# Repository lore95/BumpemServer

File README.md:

# bumpem

Host software for the IBMS Bump'em multi-directional perturbation system.

## Quick start
```sh
git clone <repo> && cd bumpem
python -m venv .venv && source .venv/bin/activate   # or conda
pip install -e ".[dev]"
pytest                                   # no hardware needed
bumpem monitor --sim                     # simulated board
```

## With hardware
No person attached for first tests. Stop the treadmill before `release` or `estop`.
```sh
pip install platformio
scripts/flash.sh                         # firmware v1  (scripts/flash.sh legacy = v0 reference)
bumpem ports                             # find the Teensy
bumpem info  --port /dev/tty.usbmodemXXXX
bumpem arm   --port /dev/tty.usbmodemXXXX --watch 3     # ramp to 5 N baseline
bumpem pulse A=95 --rise 50 --dur 600 --fall 0 --port /dev/tty.usbmodemXXXX --watch 2
bumpem release --port /dev/tty.usbmodemXXXX              # ramp to 0, drivers off
bumpem estop   --port /dev/tty.usbmodemXXXX              # drivers off now
```
Pulse amplitudes are relative to baseline. Protocol and parameters: `docs/PROTOCOL.md`.

ESCON setup is still done once in ESCON Studio. See `escon/README.md` and `docs/thesis/manual.pdf` §4.3.1.

Docs: `docs/knowledge/` (system facts), `docs/PROTOCOL.md`, `docs/STATUS.md`.

## Server
```sh
pip install -e ".[server,dev]"
bumpem serve --board sim                      # or --board /dev/tty.usbmodemXXXX
```
Open http://127.0.0.1:8000/docs to try every endpoint from the browser. API contract: `docs/API.md`.
While the server runs it owns the serial port: stop the board through the API (`POST /api/v1/estop`), not the CLI.

License: proprietary to IBMS (Institute for Advanced Biomechanics and Motion Studies, Hochschule Offenburg), non-commercial academic use only. See `LICENSE`.

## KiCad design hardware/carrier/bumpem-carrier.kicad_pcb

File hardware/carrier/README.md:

# Carrier board (v1)

Replaces the breadboard: Teensy 4.1 and the MCP4728 DAC plug into sockets, each cable module gets one 5-way **pluggable** connector: its wires are screwed into a plug once, the plug pops into the board and locks with two screws.
Same connections as `docs/diagrams/cabling-4-modules.png`, plus a protection network on each force input.

*Top view without the ground fill. Red = top copper, blue = bottom copper, yellow = silkscreen. Module wires enter at the bottom edge.*

## What is on it
| Part | Connects |
|---|---|
| U1 Teensy 4.1 (socket, USB at the left edge) | enable T27–30, force T14–17, I²C T18 SDA / T19 SCL, 3V3, GND. **VIN/5V not connected** |
| U2 Adafruit MCP4728 (socket) | VA–VD → setpoint of modules A–D, VCC 3.3 V from the Teensy |
| J1–J4 pluggable headers, one per module (A left, B front, C right, D back), pins left to right | 1 EN yellow · 2 SP+ blue · 3 SP− green · 4 GND white · 5 F brown |
| R1–R4 1 kΩ (series), R5–R8 1 MΩ (pull-down), D1–D4 BAT85 (clamp to 3.3 V) | per force input: connector F → 1 kΩ → Teensy pin; 1 MΩ to GND; BAT85 to 3.3 V |

Board 154 × 96 mm, 2 layers, through-hole parts only, 0.5 mm tracks (0.8 mm for 3.3 V), only 45° bends, ground fill on both layers (0.5 mm from other copper), 4 × M3 holes.
Spacing (measured, edge to edge): ≥ 0.74 mm between any two nets; 0.74 mm is the gap between neighbouring socket pins (2.54 mm headers).
The force tracks run under the Teensy and out past its right end, never between socket pins: ≥ 1.39 mm to any other net's pad, so a solder blob on a socket cannot reach a force signal.

**Force inputs.** The IAA100 amplifiers are trimmed to 0–3.3 V = 0–200 N (`docs/knowledge/calibration.md`). With 1 kΩ / 1 MΩ the Teensy sees 99.9 % of that (no recalibration needed). An unplugged input reads 0 N, as the ground jumpers do today. The diode only acts on a fault (amplifier mis-set or miswired): the 1 kΩ limits the current, the BAT85 dumps it into 3.3 V. If an amplifier can only be set to 0–10 V, change the pair to a divider (e.g. 22 kΩ series / 10 kΩ pull-down → 3.1 V) and recalibrate.

## Order (PCB maker)
1. Upload `fab/bumpem-carrier-gerbers.zip` to JLCPCB, Aisler, PCBWay or similar. Defaults are fine: 2 layers, 1.6 mm, any colour, HASL. The design uses no tight rules (smallest drill 0.8 mm).
2. Buy the parts below (or ask the makerspace for them).

| Qty | Part | Note |
|---|---|---|
| 1 | PCB from step 1 | |
| 2 | female header 1 × 24, 2.54 mm, 8.5 mm tall | Teensy socket (or cut from 1 × 40 strips) |
| 2 | female header 1 × 6, 2.54 mm | DAC socket |
| 4 | Phoenix Contact header **MSTB 2,5/5-GF-5,08 (1776537)**, threaded flange | on the board |
| 4 | Phoenix Contact plug **MSTB 2,5/5-STF-5,08 (1778014)**, screw flange | on each module cable: wires screwed in once (1 EN, 2 SP+, 3 SP−, 4 GND, 5 F) |
| optional | Phoenix Contact coding profile **CP-MSTB (1734634)** | keys each socket to its own plug (A's cable can't go into C's socket); check the coding scheme in Phoenix's MSTB coding guide |
| 4 | resistor 1 kΩ, 0.25 W, 1 %, axial | R1–R4 |
| 4 | resistor 1 MΩ, 0.25 W, 1 %, axial | R5–R8 |
| 4 | BAT85 Schottky diode, DO-35 | D1–D4, band (cathode) towards the 3.3 V track |
| 4 | M3 spacer + screw | |

Full list: `fab/bumpem-carrier-bom.csv`. Schematic: `fab/bumpem-carrier-schematic.pdf`. Layout: `fab/bumpem-carrier-top.pdf`, `fab/bumpem-carrier-bottom.pdf` (seen from below), both layers together `fab/bumpem-carrier-layout.pdf`. Whole KiCad project: `fab/bumpem-carrier-kicad.zip`.
**As built (2026-10-26, D23):** D1–D4 places hold **1 MΩ to 3.3 V** (not BAT85) and **R5–R8 are empty**, on purpose: a loose force cable then reads ≈ 200 N → motor 0 A + FAULT. Do not fit R5–R8.
**Soldering guide:** `fab/bumpem-carrier-soldering.pdf` (what each part looks like + German drawer names, steps 1–9 one part per page (top: where it goes, bottom: which pads), top and solder side drawn from the board, part order, diode band, extra top-side joints if the holes are not plated, checks). Rebuild: `$KPY dump_board.py bumpem-carrier.kicad_pcb fab/board.json`, then `python soldering_guide.py`.

**Makerspace HS Offenburg (reply 2026-10-05):** can make the board, but **without solder mask and silkscreen** (bare copper): fine for a prototype. Open with them: plated through-holes / vias? (the top-layer tracks end on socket pads, which cannot be soldered from the top under a socket); how to label pins without silkscreen (copper text or a printed label sheet).

## Assembly and first power-up
1. Solder the low parts first: resistors, diodes (check the band!), then the female headers, then the 4 MSTB headers (plug side at the board edge).
   **Sockets on the board are female; the male pins belong on the Teensy and the DAC** (the lab's Teensy and DAC already have them: they sit in the breadboard). Never solder male pins into the board: male meets male and nothing plugs in. Teensy and DAC are never soldered to the board, so either can be swapped. To keep the sockets straight while soldering, plug spare male pin strips into them (other ends in a breadboard) instead of the Teensy; solder one pin per end, check flat, then the rest.
2. **No Teensy, no DAC, no modules.** Multimeter beep test: 3V3 ↔ GND must **not** beep; each connector pin 3 and 4 ↔ Teensy GND must beep; connector A pin 1 ↔ Teensy socket pin 27 must beep (same for B–D: 28, 29, 30).
3. Plug in the DAC and the Teensy (USB at the board edge). USB only, no modules: `bumpem info --port <PORT>` must answer.
4. One module at a time, 48 V off: screw that module's 5 wires into a plug (order as printed on the board: EN yellow, SP+ blue, SP− green, GND white, F brown), plug it in, tighten the two flange screws. Then repeat `scripts/open_loop_test.sh` for that module.

## Before ordering: check in KiCad (5 minutes)
- Open `bumpem-carrier.kicad_pro` → PCB editor → View → 3D viewer: the MSTB headers' plug openings must face the bottom board edge.
- Hold a Teensy and the DAC over a 1:1 print of `fab/bumpem-carrier-layout.pdf`: pins over the holes, Teensy USB at the left edge.

## Change the design
Do not edit the KiCad files by hand; they are generated.
- Connections and part values: `netlist.py`. Placement and routing: `gen_carrier.py`. Schematic drawing: `gen_schematic.py`.
- Rebuild and check everything: `./build.sh` (needs KiCad 8). It must print 0 ERC violations and 0 DRC / schematic-parity violations.

Sources: Teensy 4.1 pin order from XenGi/teensy_library (MIT); MCP4728 breakout pad positions from adafruit/Adafruit-MCP4728-PCB; pins from `firmware/src/main.ino` and `docs/knowledge/wiring.md`.

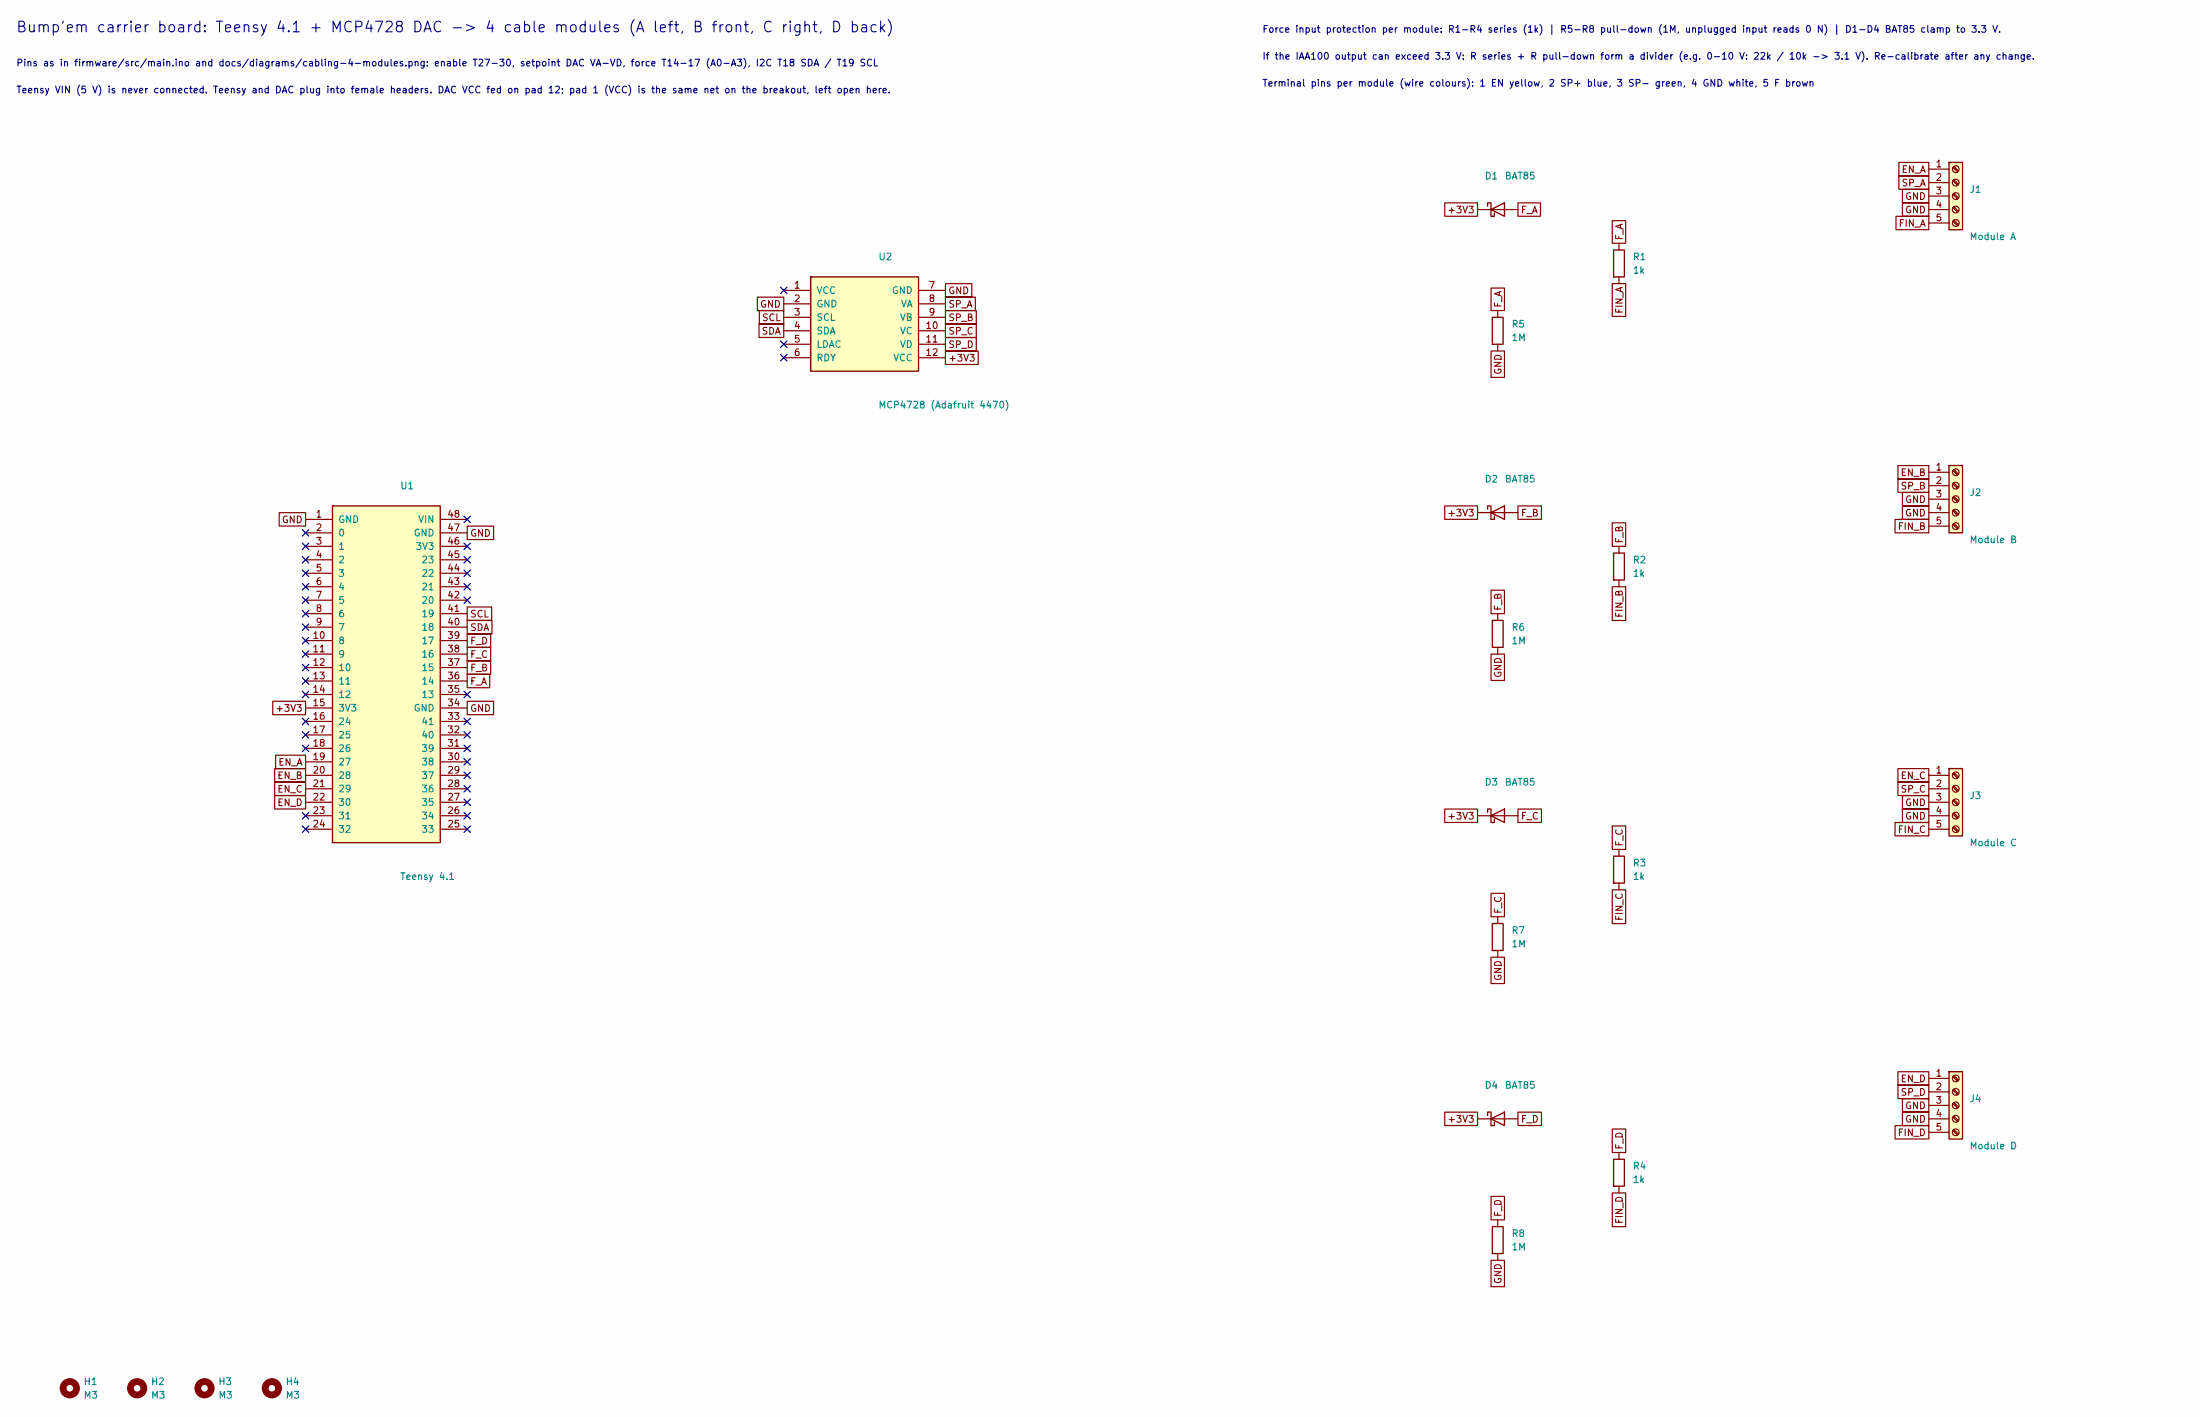
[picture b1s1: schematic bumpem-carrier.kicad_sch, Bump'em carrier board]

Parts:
D1, D2, D3, D4: BAT85; D_DO-35_SOD27_P7.62mm_Horizontal
H1, H2, H3, H4: M3; MountingHole_3.2mm_M3
J1: Module A; PhoenixContact_MSTB_2,5_5-GF-5,08_1x05_P5.08mm_Horizontal_T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
J2: Module B; PhoenixContact_MSTB_2,5_5-GF-5,08_1x05_P5.08mm_Horizontal_T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
J3: Module C; PhoenixContact_MSTB_2,5_5-GF-5,08_1x05_P5.08mm_Horizontal_T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
J4: Module D; PhoenixContact_MSTB_2,5_5-GF-5,08_1x05_P5.08mm_Horizontal_T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
R1, R2, R3, R4: 1k; R_Axial_DIN0207_L6.3mm_D2.5mm_P10.16mm_Horizontal
R5, R6, R7, R8: 1M; R_Axial_DIN0207_L6.3mm_D2.5mm_P7.62mm_Horizontal
U1: Teensy 4.1; Teensy41_Socket
U2: MCP4728 (Adafruit 4470); Adafruit_MCP4728_Socket

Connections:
+3V3: D1.1 (K), D2.1 (K), D3.1 (K), D4.1 (K), U1.15 (3V3), U2.12 (VCC)
EN_A: J1.1, U1.19 (27)
EN_B: J2.1, U1.20 (28)
EN_C: J3.1, U1.21 (29)
EN_D: J4.1, U1.22 (30)
FIN_A: J1.5, R1.2
FIN_B: J2.5, R2.2
FIN_C: J3.5, R3.2
FIN_D: J4.5, R4.2
F_A: D1.2 (A), R1.1, R5.1, U1.36 (14)
F_B: D2.2 (A), R2.1, R6.1, U1.37 (15)
F_C: D3.2 (A), R3.1, R7.1, U1.38 (16)
F_D: D4.2 (A), R4.1, R8.1, U1.39 (17)
GND: J1.3, J1.4, J2.3, J2.4, J3.3, J3.4, J4.3, J4.4, R5.2, R6.2, R7.2, R8.2, U1.1 (GND), U1.34 (GND), U1.47 (GND), U2.2 (GND), U2.7 (GND)
SCL: U1.41 (19), U2.3 (SCL)
SDA: U1.40 (18), U2.4 (SDA)
SP_A: J1.2, U2.8 (VA)
SP_B: J2.2, U2.9 (VB)
SP_C: J3.2, U2.10 (VC)
SP_D: J4.2, U2.11 (VD)

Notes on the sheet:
Bump'em carrier board: Teensy 4.1 + MCP4728 DAC -> 4 cable modules (A left, B front, C right, D back)
Pins as in firmware/src/main.ino and docs/diagrams/cabling-4-modules.png: enable T27-30, setpoint DAC VA-VD, force T14-17 (A0-A3), I2C T18 SDA / T19 SCL
Teensy VIN (5 V) is never connected. Teensy and DAC plug into female headers. DAC VCC fed on pad 12; pad 1 (VCC) is the same net on the breakout, left open here.
Force input protection per module: R1-R4 series (1k) | R5-R8 pull-down (1M, unplugged input reads 0 N) | D1-D4 BAT85 clamp to 3.3 V.
If the IAA100 output can exceed 3.3 V: R series + R pull-down form a divider (e.g. 0-10 V: 22k / 10k -> 3.1 V). Re-calibrate after any change.
Terminal pins per module (wire colours): 1 EN yellow, 2 SP+ blue, 3 SP- green, 4 GND white, 5 F brown

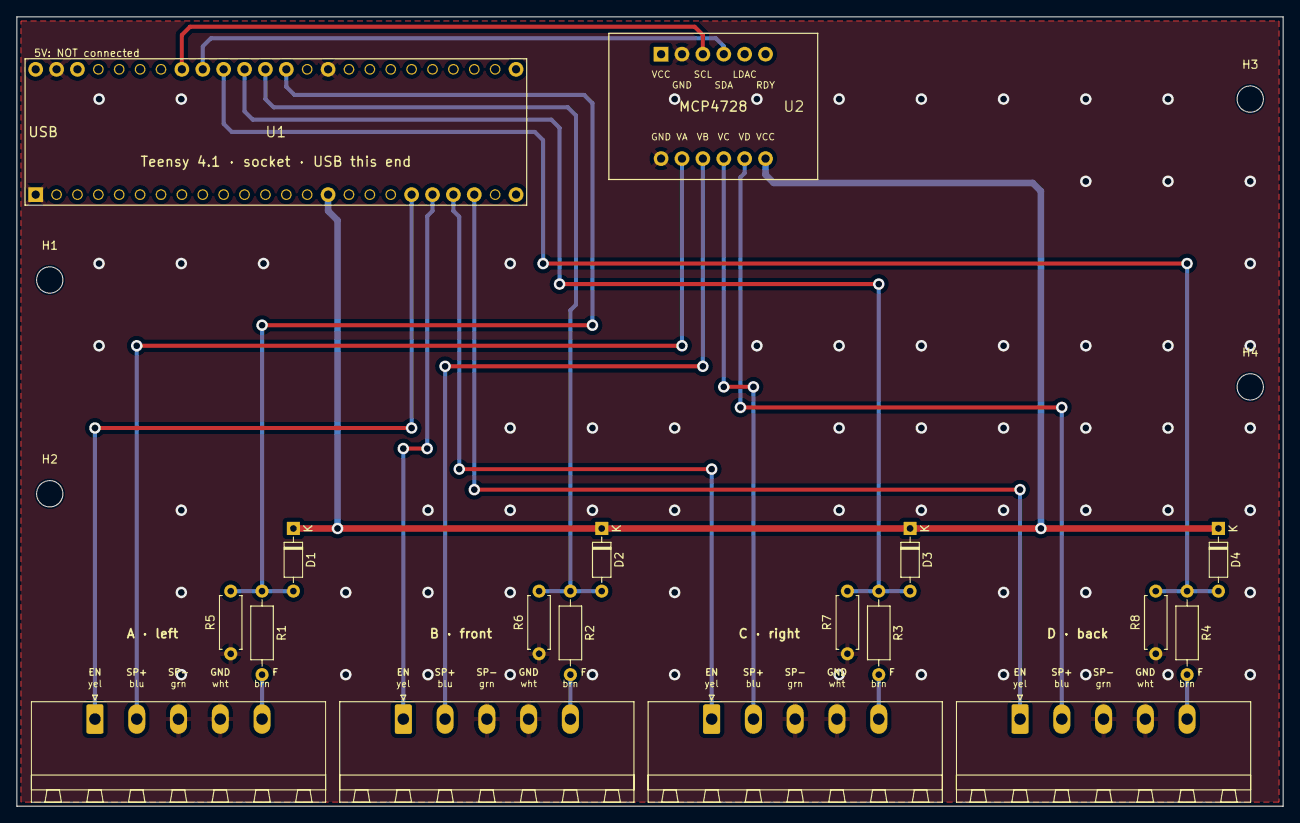
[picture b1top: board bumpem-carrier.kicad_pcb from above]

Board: 2 copper layers, 154.0 x 96.0 mm, 22 parts (0 on the bottom side), 20 nets.

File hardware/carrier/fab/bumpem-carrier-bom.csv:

"Reference","Value","Footprint","QUANTITY"
"D1-D4","BAT85","Diode_THT:D_DO-35_SOD27_P7.62mm_Horizontal","4"
"J1","Module A","Connector_Phoenix_MSTB:PhoenixContact_MSTB_2,5_5-GF-5,08_1x05_P5.08mm_Horizontal_ThreadedFlange","1"
"J2","Module B","Connector_Phoenix_MSTB:PhoenixContact_MSTB_2,5_5-GF-5,08_1x05_P5.08mm_Horizontal_ThreadedFlange","1"
"J3","Module C","Connector_Phoenix_MSTB:PhoenixContact_MSTB_2,5_5-GF-5,08_1x05_P5.08mm_Horizontal_ThreadedFlange","1"
"J4","Module D","Connector_Phoenix_MSTB:PhoenixContact_MSTB_2,5_5-GF-5,08_1x05_P5.08mm_Horizontal_ThreadedFlange","1"
"R1-R4","1k","Resistor_THT:R_Axial_DIN0207_L6.3mm_D2.5mm_P10.16mm_Horizontal","4"
"R5-R8","1M","Resistor_THT:R_Axial_DIN0207_L6.3mm_D2.5mm_P7.62mm_Horizontal","4"
"U1","Teensy 4.1","bumpem-carrier:Teensy41_Socket","1"
"U2","MCP4728 (Adafruit 4470)","bumpem-carrier:Adafruit_MCP4728_Socket","1"

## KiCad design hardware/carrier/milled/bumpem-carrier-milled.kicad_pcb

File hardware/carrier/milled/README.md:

# Carrier board, makerspace version (single-sided)

For the HS Offenburg makerspace's PCB mill: one copper layer, no plating, no solder mask, no copper fill.
Same outline, mounting holes and Teensy / DAC / plug positions as v1 (`../`), so the printed carrier plate fits and every cable plug goes in the same place.

**To make it:** send `fab/bumpem-carrier-milled.zip`. Its `gerbers/` folder is what the mill needs (bottom copper, outline, one drill file with all 114 holes, `MAKERSPACE.txt` in German and English: mill the bottom only, remove the unused copper, drill every hole). The PDFs are the 1:1 bottom view, the parts placement and the soldering guide; `bumpem-carrier-milled-sides.png` shows both sides assembled (`render_milled.py`).

## Why it is easier to solder
- **Everything is soldered on the bottom**: 70 joints, nothing on the top, no vias.
- **No ground fill**: around each pad there is bare board, so solder that misses the pad does not stick. Ask the makerspace to remove the unused copper (rub-out); otherwise isolation ≥ 0.6 mm.
- **Unused socket pins are bare holes** (no copper): nothing to solder, nothing to short. VIN cannot touch anything.
- **7 wire links** (W1–W7, insulated wire on the top, soldered underneath) instead of vias: W1 SDA, W2 SCL (crosses W1), W3 3.3 V, W4 enable B, W5–W7 setpoint A–C.
- The **1 kΩ resistors bridge tracks** too (their bodies cross the tracks between their pads). R2 has 15.24 mm leg spacing.
- Copper letters A–D next to each plug (bottom side).

## Circuit (differences from v1, D24)
Same pins as v1 (`../netlist.py`): Teensy 27–30 enable, 14–17 force, 18/19 I²C, DAC VA–VD setpoints.
Force input: plug pin 5 → 1 kΩ → Teensy pin; **1 MΩ from plug pin 5 to the same module's enable line** (plug pin 1). Armed (enable high) a loose force cable reads ≈ 200 N → that motor 0 A and over-force FAULT, as the v1 board as built (D23); disarmed it reads 0 N. No diodes, no pull-down. With the amplifier connected the 1 MΩ changes nothing measurable.
DAC ground through its row-1 GND pin only (both GND pins are joined on the breakout).

## Layout (hand-planned, `gen_milled.py`)
Ground runs round the outside: left edge, a bus under the plugs (pins 3 and 4 from below), right edge, top edge to the DAC.
Force lines go up over the Teensy's far row (F_D outermost) and come down between the Teensy and the DAC in A–D order; I²C and 3.3 V run under the Teensy and cross them on W1–W3.
Below: lanes top → bottom SP_D, EN_A, F_D, F_C, F_B, EN_D, EN_C, SP_A, FIN_A, SP_B; jumps: R1 over EN_D EN_C SP_A, R2 over EN_D EN_C SP_A SP_B, R3 over EN_D, R4 over SP_D, W5/W6 over F_D F_C EN_D EN_C, W7 over F_D F_C EN_D, W4 over SP_A FIN_A; the pull-ups R5–R8 bridge each plug's setpoint track.
(`gen_milled.py` also holds a grid router with wire-link moves; it is not used for the final layout: greedy routing needed 7–17 links and boxed nets in.)

## Build and check
`./build_milled.sh` (KiCad 8; `python3` with matplotlib for the guide): generates the board, runs DRC (must print 0 violations; the 7 "unconnected" items are W1–W7, which KiCad cannot see as wires), runs `check_milled.py` (every net one piece, counting the wire links: must print "all connected"), writes `fab/`.

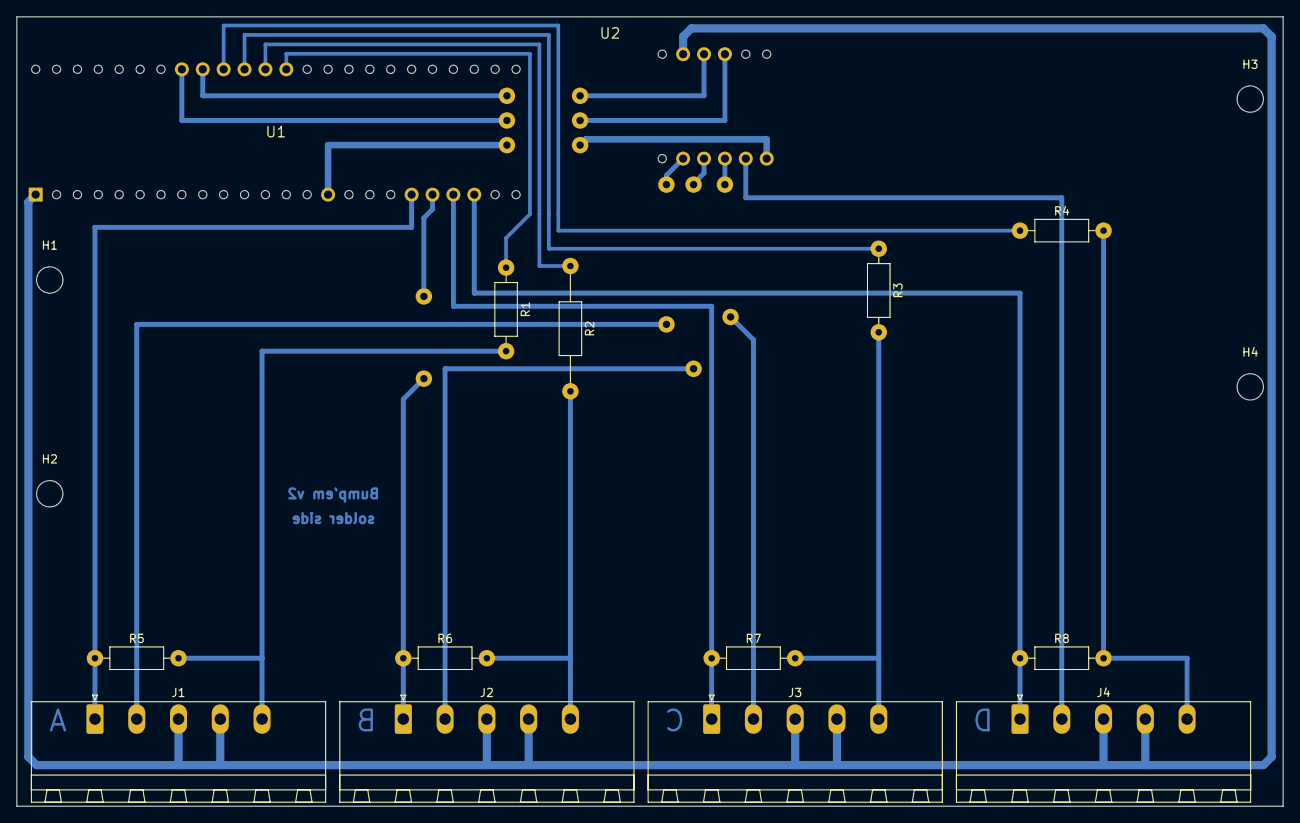
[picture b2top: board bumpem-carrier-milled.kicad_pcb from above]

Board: 2 copper layers, 154.0 x 96.0 mm, 25 parts (0 on the bottom side), 20 nets.

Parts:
H1, H2, H3, H4: M3; MountingHole_3.2mm_M3
J1: Module A; PhoenixContact_MSTB_2,5_5-GF-5,08_1x05_P5.08mm_Horizontal_T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
J2: Module B; PhoenixContact_MSTB_2,5_5-GF-5,08_1x05_P5.08mm_Horizontal_T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
J3: Module C; PhoenixContact_MSTB_2,5_5-GF-5,08_1x05_P5.08mm_Horizontal_T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
J4: Module D; PhoenixContact_MSTB_2,5_5-GF-5,08_1x05_P5.08mm_Horizontal_T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
R1, R3, R4: 1k; R_Axial_DIN0207_L6.3mm_D2.5mm_P10.16mm_Horizontal
R2: 1k; R_Axial_DIN0207_L6.3mm_D2.5mm_P15.24mm_Horizontal
R5, R6, R7, R8: 1M; R_Axial_DIN0207_L6.3mm_D2.5mm_P10.16mm_Horizontal
U1: Teensy 4.1 (socket); Teensy41_Socket_SingleSided
U2: MCP4728 (socket); MCP4728_Socket_SingleSided
W1, W2, W3, W4, W5, W6, W7: wire link; Wire_Link

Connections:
+3V3: U1.15, U2.12, W3.1, W3.2
EN_A: J1.1, R5.1, U1.19
EN_B: J2.1, R6.1, U1.20, W4.1, W4.2
EN_C: J3.1, R7.1, U1.21
EN_D: J4.1, R8.1, U1.22
FIN_A: J1.5, R1.2, R5.2
FIN_B: J2.5, R2.2, R6.2
FIN_C: J3.5, R3.2, R7.2
FIN_D: J4.5, R4.2, R8.2
F_A: R1.1, U1.36
F_B: R2.1, U1.37
F_C: R3.1, U1.38
F_D: R4.1, U1.39
GND: J1.3, J1.4, J2.3, J2.4, J3.3, J3.4, J4.3, J4.4, U1.1, U2.2
SCL: U1.41, U2.3, W2.1, W2.2
SDA: U1.40, U2.4, W1.1, W1.2
SP_A: J1.2, U2.8, W5.1, W5.2
SP_B: J2.2, U2.9, W6.1, W6.2
SP_C: J3.2, U2.10, W7.1, W7.2
SP_D: J4.2, U2.11
